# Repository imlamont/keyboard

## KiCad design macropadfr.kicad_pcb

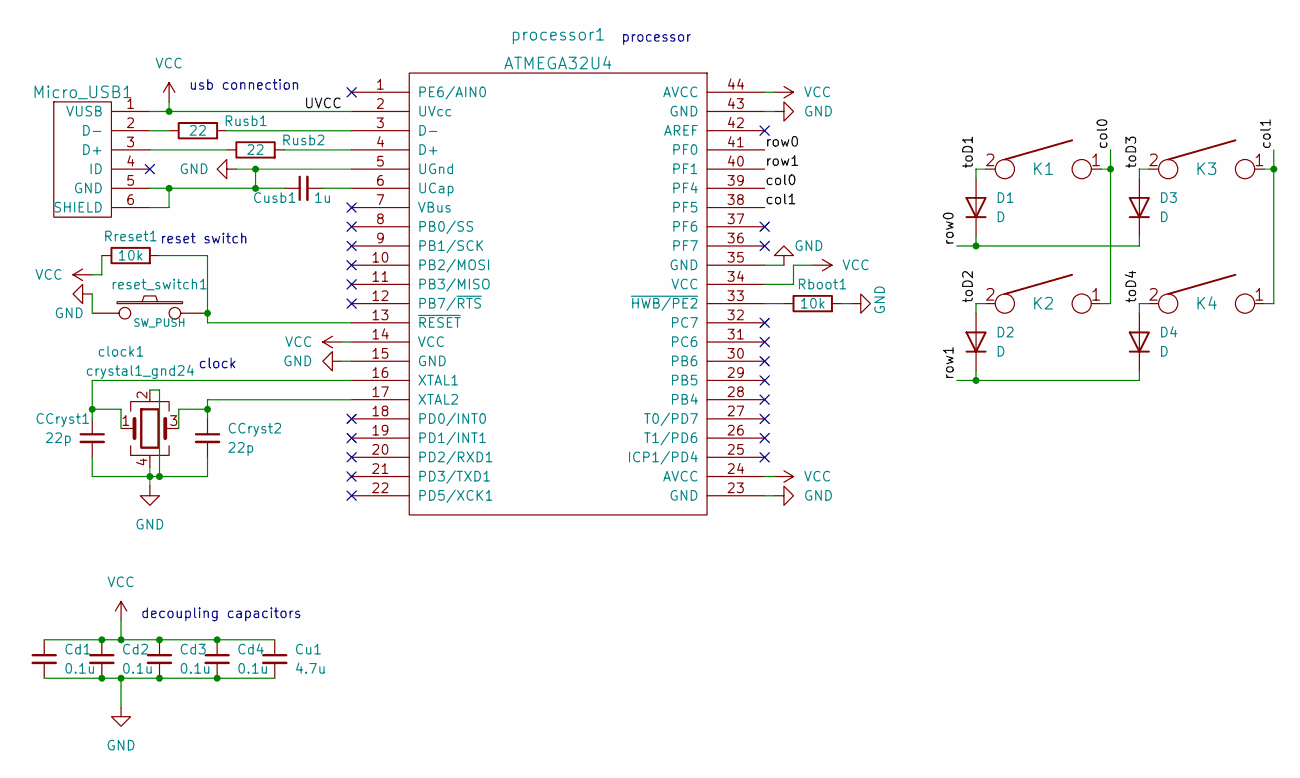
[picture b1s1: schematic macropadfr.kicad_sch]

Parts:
CCryst1, CCryst2: 22p; C_0805_2012Metric_Pad1.18x1.45mm_HandSolder
Cd1, Cd2, Cd3, Cd4: 0.1u; C_0805_2012Metric_Pad1.18x1.45mm_HandSolder
Cu1: 4.7u; C_0805_2012Metric_Pad1.18x1.45mm_HandSolder
Cusb1: 1u; C_0805_2012Metric_Pad1.18x1.45mm_HandSolder
D1, D2, D3, D4: D; D_SOD123_axial
K1, K2, K3, K4: KEYSW; Mx_Alps_100
Micro_USB1: USB_mini_micro_B; USB_miniB_hirose_5S8
Rboot1: 10k; R_0805_2012Metric_Pad1.20x1.40mm_HandSolder
Rreset1: 10k; R_0805_2012Metric_Pad1.20x1.40mm_HandSolder
Rusb1, Rusb2: 22; R_0805_2012Metric_Pad1.20x1.40mm_HandSolder
clock1: crystal1_gnd24; Crystal_SMD_Abracon_ABM8G-4Pin_3.2x2.5mm
processor1: ATMEGA32U4; LQFP-44_10x10mm_P0.8mm
reset_switch1: SW_PUSH; SW_SPST_TL3342

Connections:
/col0: K1.1, K2.1, processor1.39 (PF4)
/col1: K3.1, K4.1, processor1.38 (PF5)
/row0: D1.1 (K), D3.1 (K), processor1.41 (PF0)
/row1: D2.1 (K), D4.1 (K), processor1.40 (PF1)
/toD1: D1.2 (A), K1.2
/toD2: D3.2 (A), K3.2
/toD3: D2.2 (A), K2.2
/toD4: D4.2 (A), K4.2
GND: CCryst1.2, CCryst2.2, Cd1.2, Cd2.2, Cd3.2, Cd4.2, Cu1.2, Cusb1.1, Micro_USB1.5 (GND), Micro_USB1.6 (SHIELD), Rboot1.2, clock1.2, clock1.4, processor1.5 (UGnd), processor1.15 (GND), processor1.23 (GND), processor1.35 (GND), processor1.43 (GND), reset_switch1.1; also elsewhere on the board
unnamed: CCryst1.1, clock1.1, processor1.16 (XTAL1)
unnamed: CCryst2.1, clock1.3, processor1.17 (XTAL2)
unnamed: Cusb1.2, processor1.6 (UCap)
unnamed: Micro_USB1.2 (D-), Rusb1.1
unnamed: Micro_USB1.3 (D+), Rusb2.1
unnamed: Rboot1.1, processor1.33 (~HWB/PE2)
unnamed: Rreset1.2, processor1.13 (~RESET), reset_switch1.2
unnamed: Rusb1.2, processor1.3 (D-)
unnamed: Rusb2.2, processor1.4 (D+)
VCC: Cd1.1, Cd2.1, Cd3.1, Cd4.1, Cu1.1, Micro_USB1.1 (VUSB), Rreset1.1, processor1.2 (UVcc), processor1.14 (VCC), processor1.24 (AVCC), processor1.34 (VCC), processor1.44 (AVCC); also elsewhere on the board

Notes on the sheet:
clock
reset switch
processor
decoupling capacitors
usb connection

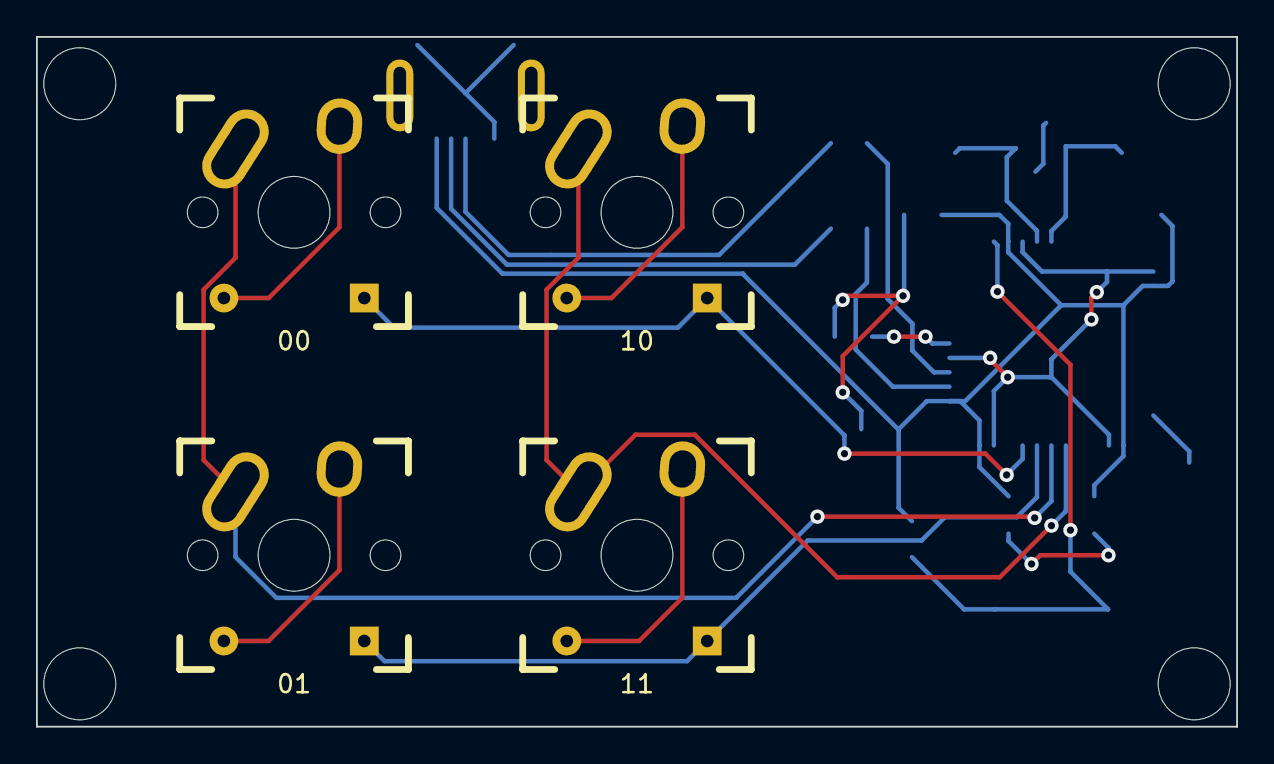
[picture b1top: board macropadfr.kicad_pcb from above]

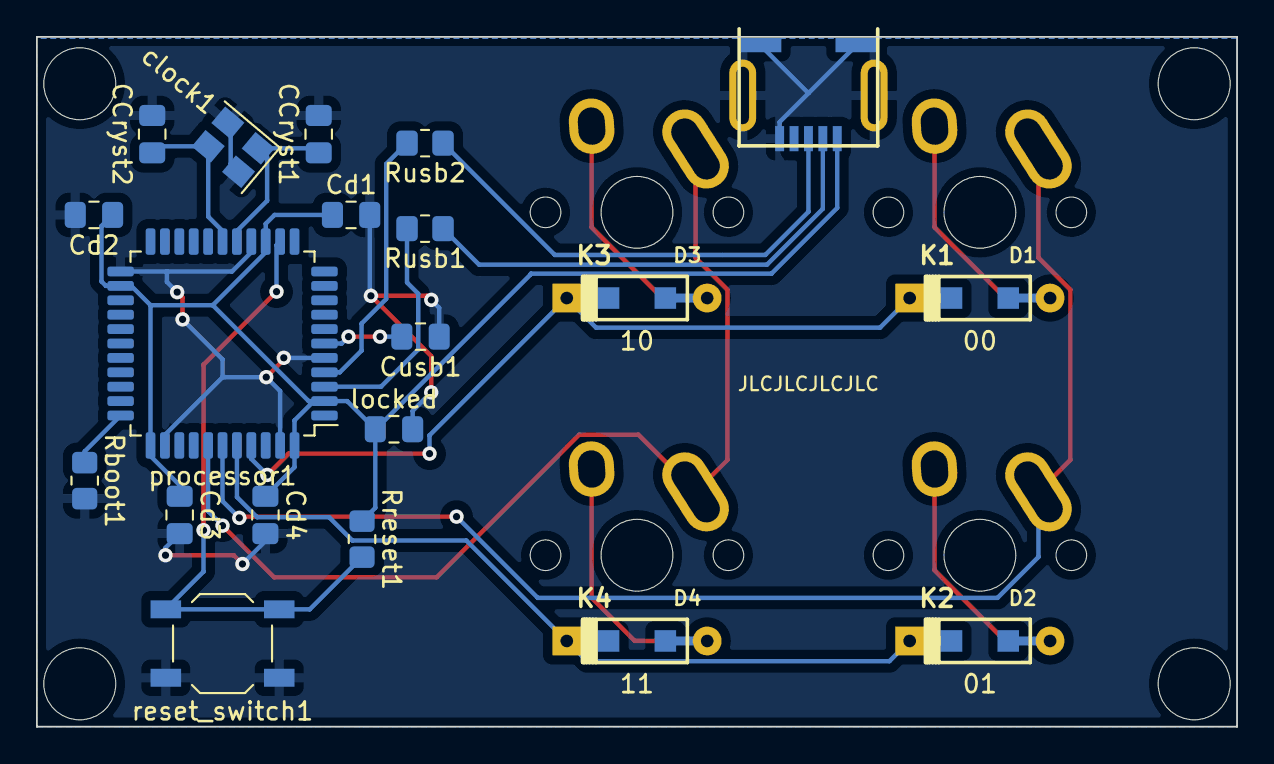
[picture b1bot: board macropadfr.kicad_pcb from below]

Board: 2 copper layers, 66.7 x 38.3 mm, 24 parts (20 on the bottom side), 19 nets.

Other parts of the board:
locked: locked; C_0805_2012Metric_Pad1.18x1.45mm_HandSolder

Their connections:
GND: locked.2; also elsewhere on the board
VCC: locked.1; also elsewhere on the board

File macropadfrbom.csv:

"Id";"Designator";"Package";"Quantity";"Designation";"Supplier and ref";
1;"K1,K4,K3,K2";"Mx_Alps_100";4;"KEYSW";;;
2;",,";"";3;"";;;
3;"REF**";"throughhole4mm";1;"throughhole4mm";;;
4;"Rusb1,Rusb2";"R_0805_2012Metric_Pad1.20x1.40mm_HandSolder";2;"22";;;
5;"reset_switch1";"SW_SPST_TL3342";1;"SW_PUSH";;;
6;"Cusb1";"C_0805_2012Metric_Pad1.18x1.45mm_HandSolder";1;"1u";;;
7;"D3,D2,D4,D1";"D_SOD123_axial";4;"D";;;
8;"Micro_USB1";"USB_miniB_hirose_5S8";1;"USB_mini_micro_B";;;
9;"clock1";"Crystal_SMD_Abracon_ABM8G-4Pin_3.2x2.5mm";1;"crystal1_gnd24";;;
10;"CCryst2,CCryst1";"C_0805_2012Metric_Pad1.18x1.45mm_HandSolder";2;"22p";;;
11;"Cd1,Cd2,Cd4,Cd3";"C_0805_2012Metric_Pad1.18x1.45mm_HandSolder";4;"0.1u";;;
12;"processor1";"LQFP-44_10x10mm_P0.8mm";1;"ATMEGA32U4";;;
13;"Rreset1,Rboot1";"R_0805_2012Metric_Pad1.20x1.40mm_HandSolder";2;"10k";;;
14;"Cu1";"C_0805_2012Metric_Pad1.18x1.45mm_HandSolder";1;"4.7u";;;

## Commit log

2022-02-25 test
2022-02-25 messed with the crystal and some pcb stuff
2022-02-27 deleted: _autosave-macropadfr.kicad_pcb deleted: macropadfr-backups/macropadfr-2022-02-24_200521.zip new file: macropadfr-backups/macropadfr-2022-02-25_095033.zip new file: macropadfr-backups/macropa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
2022-02-27 rough draft done?
2022-02-28 fixed some problems with connections
2022-04-18 bom and gerbers for final
2022-04-18 didnt save now did
